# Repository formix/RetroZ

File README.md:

# RetroZ SBC S80
A minimalist single board Z80 retro computer based on the S80 design 
specifications.

This board is developped using the S80 physical specifications. The 
specifications are not currently available online but I plan to fix that in a 
future revision.

*Front of the board*

[Back of the board](https://raw.githubusercontent.com/formix/RetroZ/master/Documents/RetroZ-SBC-Back.png)

You can find the board schematic as a PDF [here](https://github.com/formix/RetroZ/blob/master/Documents/RetroZ-SBC.pdf).

## BOM

You can download the BOM [here](https://github.com/formix/RetroZ/blob/master/Projects/RetroZ-SBC/RetroZ-SBC-BOM.ods?raw=true). It is an Open Document Worksheet file and you should be able to open it with Open/Libre Office or MS Excel. If you have issue, contact me.

| Comp.                      | Mouser#  | Digikey#      | Mfr#               | Qty | Description                        | 
|----------------------------|----------|---------------|--------------------|-----|------------------------------------| 
| C1,C2                      |          |               | C317C200J5G5TA     | 2   | 20pf Capacitor                     | 
| C3,C4                      |          |               | FG28C0G1H470JNT06  | 2   | 47pF Capacitor                     | 
| C5,C6,C7,C8,C9,C10,C11,C12 |          |               | C322C104K5R5TA7301 | 8   | 0,1uF Capacitors                   | 
| D1                         |          |               | 151051VS04000      | 1   | Green Led 5mm                      | 
| D2,D3                      |          |               | 151031SS06000      | 2   | Red Led 3mm Round, FwdV 2.2        | 
| IC1                        |          |               | ADM803TAKSZ-REEL7  | 1   | Power-on Reset chip                | 
| IC2                        |          |               | AT28C256-15PU      | 1   | EEPROM 256kbit 28-Pin PDIP         | 
| IC2,IC3                    |          |               | 4828-6004-CP       | 2   | CONN IC DIP SOCKET 28POS TIN       | 
| IC3                        |          |               | AS6C62256-55PCN    | 1   | IC SRAM 256K PARALLEL 28DIP        | 
| J1                         | 485-2223 | 1528-1385-ND  | 2223               | 1   | Adafruit stacking header 2x20      | 
| J2,J3                      | 485-85   | 1528-1074-ND  | 85                 | 1   | STACKING HEADER ARDUINO SHIELD     | 
| J4                         |          |               | PRPC005DAAN-RC     | 1   | 5x2 Pin Connector                  | 
| J4,J6                      |          |               | QPC02SXGN-RC       | 2   | 1x2 Shunt connector                | 
| J5                         |          |               | 629105150521       | 1   | USB Microb B SMT Connector         | 
| J6                         |          |               | PRPC004DAAN-RC     | 1   | 4x2 Pin Connector                  | 
| R1                         |          |               | RNF14FTD1M00       | 1   | 1M Ohm Resistor                    | 
| R10,R11                    |          |               | RNF14FTD332R       | 2   | 332 Ohm resistor                   | 
| R2                         |          |               | RNF14FTD1K00       | 1   | 1k Ohm Resistor                    | 
| R3,R4,R5,R6,R12,R13,R14    |          |               | RNF14FTD10K0       | 7   | 10k Ohm Resistor                   | 
| R7                         |          |               | RNF14FTD221R       | 1   | 221 Ohm Resistor                   | 
| R8,R9                      |          |               | RNF14FTD27R4       | 2   | 27 Ohm Resistors                   | 
| SW2                        |          |               | BD01               | 1   | DIP Switch x1                      | 
| U1                         |          |               | 74LS32             | 1   | Quand OR                           | 
| U2                         |          |               | 74HCT04            | 1   | Hex Inverter Schmidt Trigger       | 
| U3                         |          |               | Z84C0008PEG        | 1   | Z80 CPU                            | 
| U3,U5                      |          |               | 4840-6004-CP       | 1   | 40 pin (2 x 20) DIP socket 15,24mm | 
| U4                         |          |               | SN74LS138N         | 1   | 3 to 8 Decoder/Demux               | 
| U5                         |          |               | Z84C4208PEG        | 1   | Z80 SIO/2                          | 
| U6                         |          |               | FT230XS-U          | 1   | UART to USB                        | 
| U7                         |          |               | 74LS92             | 1   | Dodecade counter (div. By 12)      | 
| Y1                         |          |               | ECS-73-20-5PX-TR   | 1   | 7,3728 MHz Crystal                 | 

## Development Note

### 2019-01-15
The review phase is done! I just sent the board to production. I should get the
finished board next week.

### 2019-01-26
I recieved my boards (10 boards!) yesterday. I just finished creating the BOM 
and sorted through my parts to order what is missing. I expect to recieve my 
order in the coming week. I'll work on the NASCOM Basic once I got the 
computer assembled. Stay tuned!

### 2019-08-03
It's been a while since I updated that README file but as you can see,
I'm committing regularily on the project. Simply put, I'm too busy playing 
with my working RetroZ SBC computer to update the front documentation. It is 
time to fix that, continue reading to get the full update.

## What's Inside?
The RetroZ-SBC computer is a 8MHz Z80 CPU clocked at 7.3728 MHz. It supports 
up to 32kB of ROM and 32kB of RAM. An SIO/2 chip is connected to the USB 
Micro B socket using an FTDI serial converter. Rx and Tx leds let you know 
when the computer communicates over USB. The whole computer is powered through
the same USB port and a power-on reset monitor resets the computer at startup.
A Reset button allows warm computer restart. An On/Off DIP switch controls the
power state of the computer and a power led indicator let you know that the 
beast is powered. All the Z80 processor pins are available through the 40 pins
stacking header plus some other on the User Port A. User Port B stacking
header is fully available (8 pins) for child boards future projects.

## The Connection
The USB to serial conversion is made possible thanks to an FTDI chip 
[behind the board](https://raw.githubusercontent.com/formix/RetroZ/master/Documents/RetroZ-SBC-Back.png) 
and is clocked at 115200 bauds by default. This speed can be changed 
programmatically through the Z84C40 (Zilog SIO/2) registers. On a Windows
machine the device can be accessed using **COM5**. For a 
Mac/Linux box it is **/dev/ttyUSB0**. Hardware flow control CTS/RTS is fully 
wired so feel free to flood the console with whatever you get, it should 
handle it.

## Technical Reference
### Power and commnunication over USB
Using a single USB Micro-B wire, it is possible to power-up and communicate 
with the computer. There is a DIP switch to set the computer on or off and a 
power indicator led indicates when the computer is powered on. There is also
a power line monitor chip (IC1) that pull the /RESET line LOW for 240 ms 
after power on.

### Serial Communication
Serial communication is achieved using a Z84C42 SIO/2 chip. The serial port A 
is connected to the USB jack through an FTDI UART to USB 2.0 converter. Rx 
and Tx leds indicate when communication occurs on that port. The serial port 
B is connected back into the User Port A (J2) PIN 2 (RxB) and Pin 3 (TxB) for 
slave cards serial communications.

**The serial port A clock** is directly tied to the clock and can be changed 
programmatically from the SIO/2 registers. In the NASCOM Basic provided, it is 
set to 115200 by default.

**The serial port B clock** The default speed is set to 115200 bauds as well. 
Again, that speed can be programmatically changed. The serial clock on port B 
goes through a dodecade counter and can be further adjusted using the 
`Clock div.` (J6) jumper that offers another set of 1,2,6 and 12 dividers. 
That gives a wide variety of standard baud rates down to 9600 bauds.

### Onboard memory control
The PIN 1 of the User Port A is pulled low with a 2k resistor. This is the 
on-board memory enable input pin (/ME). To disable onboard memory, an 
expansion card can set that pin HIGH. This would be the case with a memory 
expansion board. It can be hardwired to 5V to disable the onboard memory 
completely or it can be tied to some logic to leverage the on-board memory as 
needed.

### Interrupt Chaining
The RetroZ SBC design allows chaining interrupts of up to 4 slave boards. The
onboard SIO/2 IEO pin is hardwired to the User Port A INT0 (PIN 4). Its 
Interrupt Enable In pin can be tied to any of the other INT pins using the 
IEI Select jumper (J4). Selecting the first position of that jumper (INT0) 
sets the on-board SIO/2 as the Master. On slave boards, the Interrupt Enable 
In will have 6 positions. Also, a 4 positions IEO jumper header should be 
provided to select the right User Port A IEO position (pins 5-8). More on 
that on the slave board design document.

**WARNING** User Port A pins 4-8 (interrupts) are not protected. If you 
connect a daughter board without checking jumper settings first, you could 
short an IO pin on your stack and damage a chip! Looking into a solution to 
that in a future revision.

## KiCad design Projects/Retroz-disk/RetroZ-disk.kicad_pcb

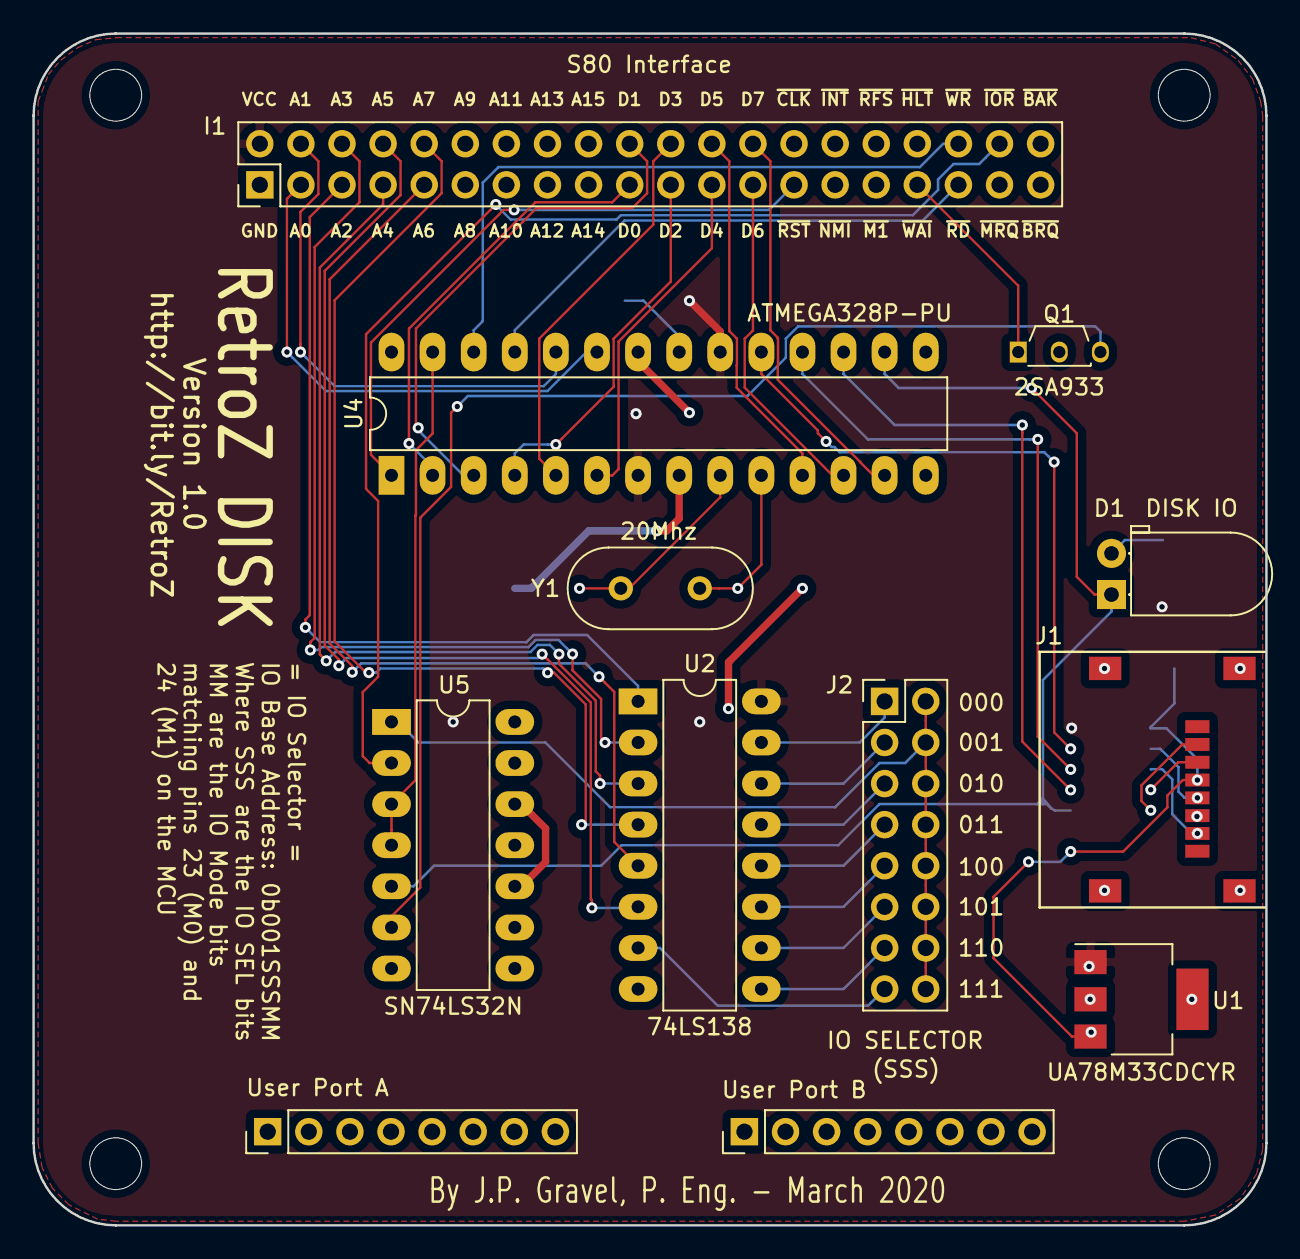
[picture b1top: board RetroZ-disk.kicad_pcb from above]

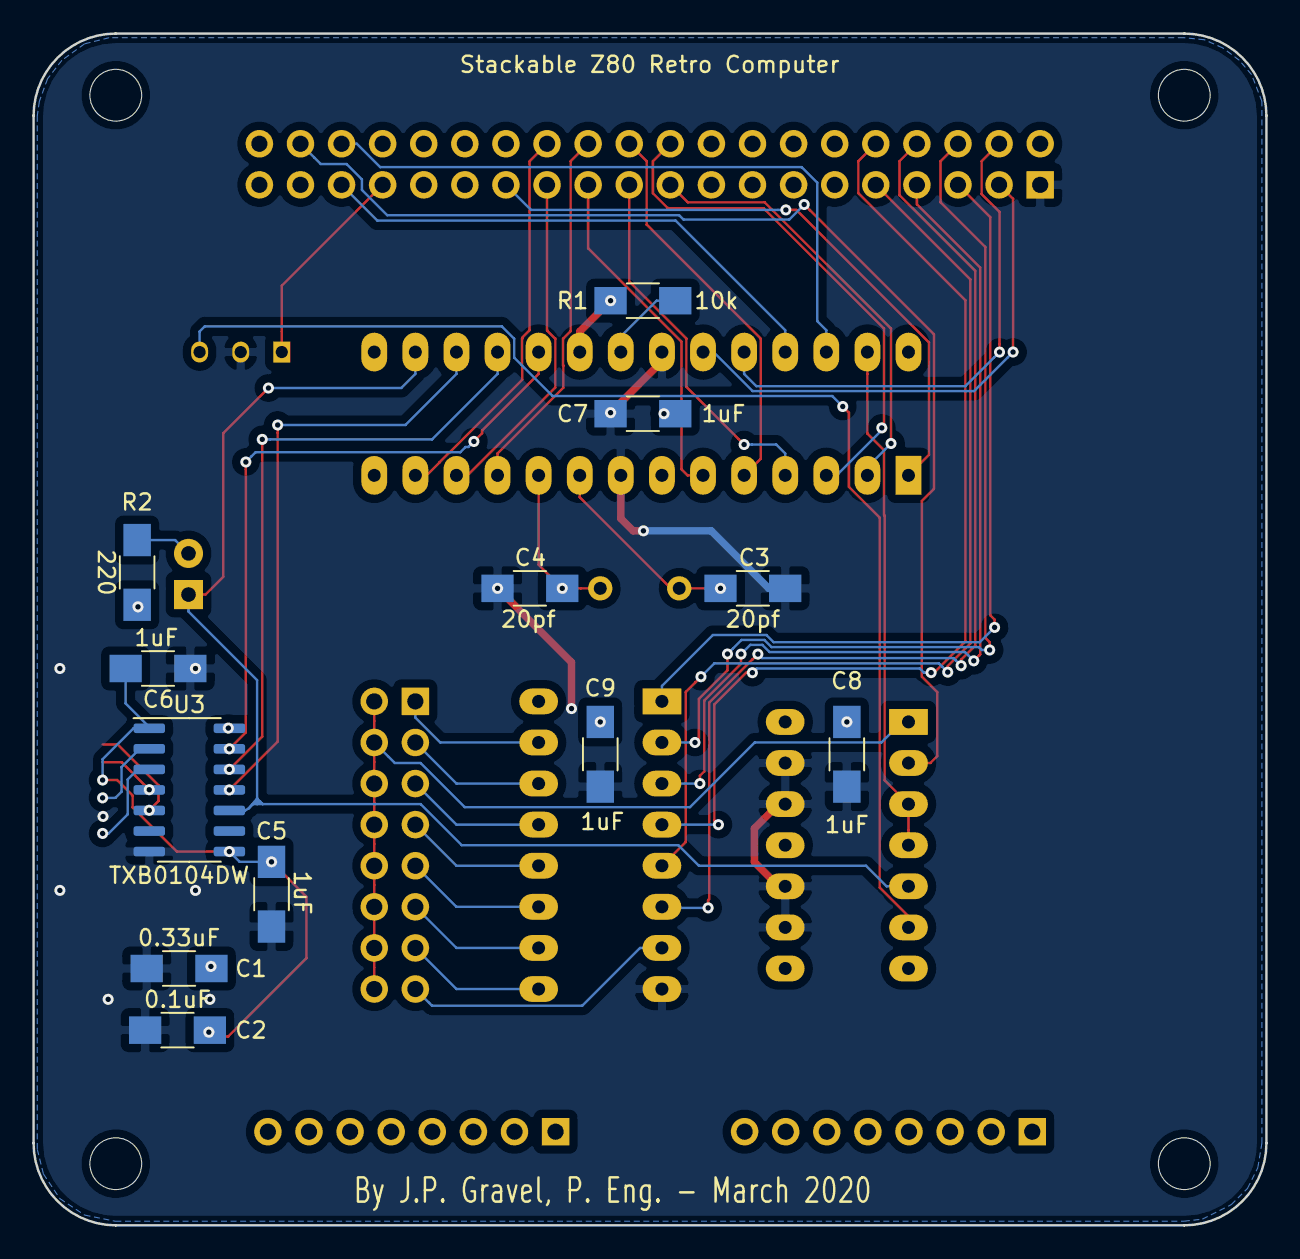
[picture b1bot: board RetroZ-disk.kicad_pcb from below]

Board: 2 copper layers, 76.2 x 73.7 mm, 22 parts (12 on the bottom side), 47 nets.

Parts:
C1: 0.33uF; R_1206_HandSoldering
C2: 0.1uF; R_1206_HandSoldering
C3, C4: 20pf; R_1206_HandSoldering
C5, C6, C7, C8, C9: 1uF; R_1206_HandSoldering
D1: DISK IO; LED_D5.0mm_Horizontal_O1.27mm_Z3.0mm
I1: S80 Interface; S80-1
J1: Micro_SD_Card; MicroSd_Wurth_693072010801
J2: IO SELECTOR; Pin_Header_Straight_2x08_Pitch2.54mm
Q1: 2SA933; TO-92S_Wide
R1: 10k; R_1206_HandSoldering
R2: 220; R_1206_HandSoldering
U1: UA78M33CDCYR; SOT-223-3_TabPin2
U2: 74LS138; DIP-16_W7.62mm_LongPads
U3: TXB0104DW; SOIC-14_3.9x8.7mm_P1.27mm
U4: ATMEGA328P-PU; DIP-28_W7.62mm_LongPads
U5: SN74LS32N; DIP-14_W7.62mm_LongPads
Y1: 20Mhz; Crystal_HC49-4H_Vertical

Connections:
/D0: I1.19, U4.2
/D1: I1.20, U4.3
/D2: I1.21, U4.4
/D3: I1.22, U4.5
/D4: I1.23, U4.6
/D5: I1.24, U4.11
/D6: I1.25, U4.12
/D7: I1.26, U4.13
/MISO: U3.12, U4.18
/MODE0: I1.3, U4.23
/MODE1: I1.4, U4.24
/MOSI: U3.11, U4.17
/SCK: U3.13, U4.19
/~CS: U4.27, U5.3, U5.4
/~IORQ: I1.38, U5.2
/~RD: I1.35, U4.25
/~RESET: I1.27, U4.1
/~SEL: J2.2, J2.4, J2.6, J2.8, J2.10, J2.12, J2.14, J2.16, U5.1
/~SS: D1.1, U3.10, U4.16, U5.5
/~WAIT: I1.33, Q1.1
/~WR: I1.36, U4.26
GND: C1.2, C2.2, C3.2, C4.2, C5.2, C6.2, C7.2, C8.2, C9.2, I1.1, J1.6, J1.9, Q1.2, U1.2, U2.8, U3.7, U4.8, U4.22, U5.9, U5.10, U5.12, U5.13
unnamed: C3.1, U4.9, Y1.2
unnamed: C4.1, U4.10, Y1.1
unnamed: D1.2, R2.2
unnamed: I1.5, U2.1
unnamed: I1.6, U2.2
unnamed: I1.7, U2.3
unnamed: I1.8, U2.6
unnamed: I1.9, U2.5
unnamed: I1.10, U2.4
unnamed: J1.2, U3.5
unnamed: J1.3, U3.4
unnamed: J1.5, U3.2
unnamed: J1.7, U3.3
unnamed: J2.1, U2.15
unnamed: J2.3, U2.14
unnamed: J2.5, U2.13
unnamed: J2.7, U2.12
unnamed: J2.9, U2.11
unnamed: J2.11, U2.10
unnamed: J2.13, U2.9
unnamed: J2.15, U2.7
unnamed: Q1.3, U5.6
unnamed: R1.1, U4.21
VCC: C1.1, C7.1, C8.1, C9.1, I1.2, R1.2, R2.1, U1.1, U2.16, U3.14, U4.7, U4.20
VDD: C2.1, C5.1, C6.1, J1.4, U1.3, U3.1, U3.8

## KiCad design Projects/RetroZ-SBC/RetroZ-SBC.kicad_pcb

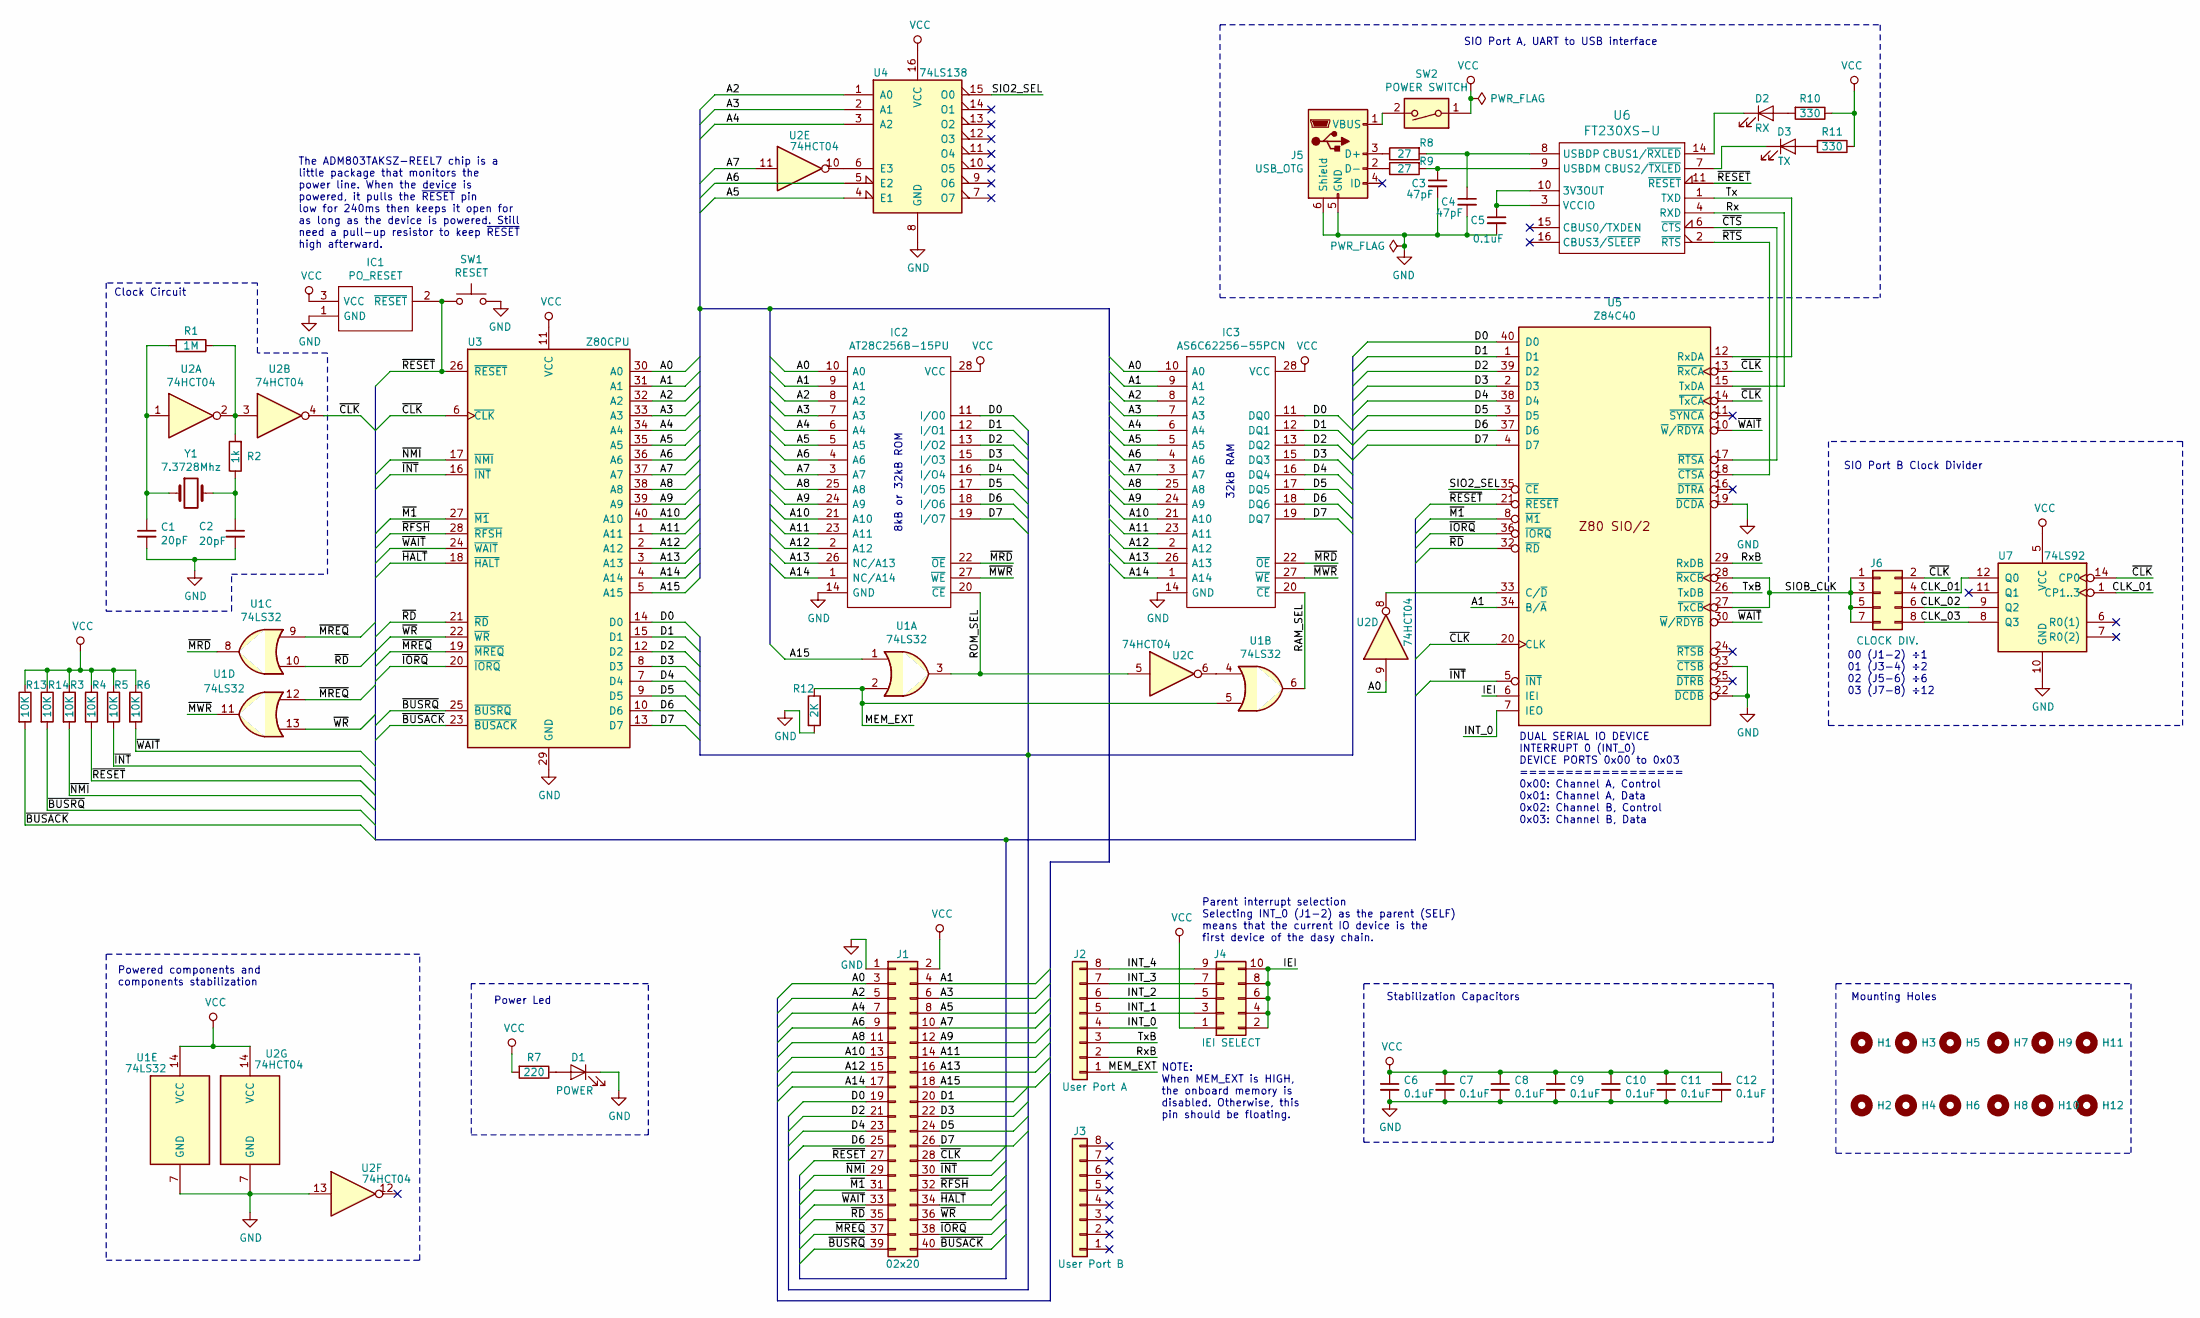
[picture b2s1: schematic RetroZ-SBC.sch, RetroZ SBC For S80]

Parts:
C1, C2: 20pF; C_Disc_D3.4mm_W2.1mm_P2.50mm; Mfr# C317C200J5G5TA
C3, C4: 47pF; C_Disc_D3.4mm_W2.1mm_P2.50mm; Mfr# FG28C0G1H470JNT06
C5, C6, C7, C8, C9, C10, C11, C12: 0.1uF; C_Disc_D3.4mm_W2.1mm_P2.50mm; Mfr# C322C104K5R5TA7301
D1: POWER; LED_D5.0mm_Horizontal_O1.27mm_Z3.0mm; Mfr# 151051VS04000
D2: RX; LED_D3.0mm_Horizontal_O1.27mm_Z2.0mm; Mfr# 151031SS06000
D3: TX; LED_D3.0mm_Horizontal_O1.27mm_Z2.0mm; Mfr# 151031SS06000
H1, H2, H3, H4, H5, H6, H7, H8, H9, H10, H11, H12: MountingHole; MountingHole_3.2mm_M3
IC1: PO_RESET; SOT-23; Mfr# ADM803TAKSZ-REEL7
IC2: AT28C256B-15PU; DIP-28_W15.24mm; Mouser Part Number 556-AT28C25615PU
IC3: AS6C62256-55PCN; DIP-28_W15.24mm; Mouser Part Number 913-AS6C62256-55PCN
J1: 02x20; Pin_Header_Straight_2x20_Pitch2.54mm; Mfr# 2223
J2: User Port A; Pin_Header_Straight_1x08_Pitch2.54mm
J3: User Port B; Pin_Header_Straight_1x08_Pitch2.54mm
J4: IEI SELECT; Pin_Header_Straight_2x05_Pitch2.54mm; Mfr# PRPC005DAAN-RC
J5: USB_OTG; USB_Micro-B_Wuerth-629105150521_CircularHoles; Mfr# 629105150521
J6: CLOCK DIV.; Pin_Header_Straight_2x04_Pitch2.54mm; Mfr# PRPC004DAAN-RC
R1: 1M; R_Axial_DIN0207_L6.3mm_D2.5mm_P10.16mm_Horizontal; Mfr# RNF14FTD1M00
R2: 1k; R_Axial_DIN0207_L6.3mm_D2.5mm_P10.16mm_Horizontal; Mfr# RNF14FTD1K00
R3, R4, R5, R6, R13, R14: 10K; R_Axial_DIN0207_L6.3mm_D2.5mm_P10.16mm_Horizontal; Mfr# RNF14FTD10K0
R7: 220; R_Axial_DIN0204_L3.6mm_D1.6mm_P2.54mm_Vertical; Mfr# RNF14FTD221R
R8, R9: 27; R_Axial_DIN0204_L3.6mm_D1.6mm_P2.54mm_Vertical; Mfr# RNF14FTD27R4
R10, R11: 330; R_Axial_DIN0204_L3.6mm_D1.6mm_P2.54mm_Vertical; Mfr# RNF14FTD330R
R12: 2K; R_Axial_DIN0207_L6.3mm_D2.5mm_P10.16mm_Horizontal; Mfr# RNF14FTD10K0
SW1: RESET; SW_PUSH_6mm_h5mm; Mfr# MJTP1230
SW2: POWER SWITCH; SW_DIP_x1_W7.62mm_Slide; Mfr# BD01
U1: 74LS32; DIP-14_W7.62mm
U2: 74HCT04; DIP-14_W7.62mm; Mfr# 74HCT04
U3: Z80CPU; DIP-40_W15.24mm; Mfr# Z84C0008PEG
U4: 74LS138; DIP-16_W7.62mm; Mfr# SN74LS138N
U5: Z84C40; DIP-40_W15.24mm; Mfr# Z84C4208PEG
U6: FT230XS-U; TSSOP-16_4.4x5mm_Pitch0.65mm; Mfr# FT230XS-U
U7: 74LS92; DIP-14_W7.62mm; Mfr# 74LS92
Y1: 7.3728Mhz; Crystal_SMD_SeikoEpson_MC405-2pin_9.6x4.1mm_HandSoldering; Mfr# ECS-73-20-5PX-TR

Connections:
/A0: IC2.10 (A0), IC3.10 (A0), J1.3, U2.9, U3.30 (A0)
/A1: IC2.9 (A1), IC3.9 (A1), J1.4, U3.31 (A1), U5.34 (B/~A)
/A2: IC2.8 (A2), IC3.8 (A2), J1.5, U3.32 (A2), U4.1 (A0)
/A3: IC2.7 (A3), IC3.7 (A3), J1.6, U3.33 (A3), U4.2 (A1)
/A4: IC2.6 (A4), IC3.6 (A4), J1.7, U3.34 (A4), U4.3 (A2)
/A5: IC2.5 (A5), IC3.5 (A5), J1.8, U3.35 (A5), U4.4 (E1)
/A6: IC2.4 (A6), IC3.4 (A6), J1.9, U3.36 (A6), U4.5 (E2)
/A7: IC2.3 (A7), IC3.3 (A7), J1.10, U2.11, U3.37 (A7)
/A8: IC2.25 (A8), IC3.25 (A8), J1.11, U3.38 (A8)
/A9: IC2.24 (A9), IC3.24 (A9), J1.12, U3.39 (A9)
/A10: IC2.21 (A10), IC3.21 (A10), J1.13, U3.40 (A10)
/A11: IC2.23 (A11), IC3.23 (A11), J1.14, U3.1 (A11)
/A12: IC2.2 (A12), IC3.2 (A12), J1.15, U3.2 (A12)
/A13: IC2.26 (NC/A13), IC3.26 (A13), J1.16, U3.3 (A13)
/A14: IC2.1 (NC/A14), IC3.1 (A14), J1.17, U3.4 (A14)
/A15: J1.18, U1.1, U3.5 (A15)
/CLK_01: J6.4, U7.1 (CP1..3), U7.12 (Q0)
/CLK_02: J6.6, U7.9 (Q2)
/CLK_03: J6.8, U7.8 (Q3)
/D0: IC2.11 (I/O0), IC3.11 (DQ0), J1.19, U3.14 (D0), U5.40 (D0)
/D1: IC2.12 (I/O1), IC3.12 (DQ1), J1.20, U3.15 (D1), U5.1 (D1)
/D2: IC2.13 (I/O2), IC3.13 (DQ2), J1.21, U3.12 (D2), U5.39 (D2)
/D3: IC2.15 (I/O3), IC3.15 (DQ3), J1.22, U3.8 (D3), U5.2 (D3)
/D4: IC2.16 (I/O4), IC3.16 (DQ4), J1.23, U3.7 (D4), U5.38 (D4)
/D5: IC2.17 (I/O5), IC3.17 (DQ5), J1.24, U3.9 (D5), U5.3 (D5)
/D6: IC2.18 (I/O6), IC3.18 (DQ6), J1.25, U3.10 (D6), U5.37 (D6)
/D7: IC2.19 (I/O7), IC3.19 (DQ7), J1.26, U3.13 (D7), U5.4 (D7)
/IEI: J4.2, J4.4, J4.6, J4.8, J4.10, U5.6 (IEI)
/INT_0: J2.4, U5.7 (IEO)
/INT_1: J2.5, J4.3
/INT_2: J2.6, J4.5
/INT_3: J2.7, J4.7
/INT_4: J2.8, J4.9
/MEM_EXT: J2.1, R12.1, U1.2, U1.5
/RAM_SEL: IC3.20 (~CE), U1.6
/ROM_SEL: IC2.20 (~CE), U1.3, U2.5
/Rx: U5.15 (TxDA), U6.4 (RXD)
/RxB: J2.2, U5.29 (RxDB)
/SIO2_SEL: U4.15 (O0), U5.35 (~CE)
/SIOB_CLK: J6.1, J6.3, J6.5, J6.7, U5.27 (~TxCB), U5.28 (~RxCB)
/Tx: U5.12 (RxDA), U6.1 (TXD)
/TxB: J2.3, U5.26 (TxDB)
/~BUSACK: J1.40, R13.2, U3.23 (~BUSACK~)
/~BUSRQ: J1.39, R14.2, U3.25 (~BUSRQ~)
/~CLK: J1.28, J6.2, U2.4, U3.6 (~CLK~), U5.13 (~RxCA), U5.14 (~TxCA), U5.20 (CLK), U7.14 (CP0)
/~CTS: U5.17 (~RTSA), U6.6 (~CTS)
/~HALT: J1.34, U3.18 (~HALT~)
/~INT: J1.30, R5.2, U3.16 (~INT~), U5.5 (~INT)
/~IORQ: J1.38, U3.20 (~IORQ~), U5.36 (~IORQ)
/~M1: J1.31, U3.27 (~M1~), U5.8 (~M1)
/~MRD: IC2.22 (~OE), IC3.22 (~OE), U1.8
/~MREQ: J1.37, U1.9, U1.12, U3.19 (~MREQ~)
/~MWR: IC2.27 (~WE), IC3.27 (~WE), U1.11
/~NMI: J1.29, R3.2, U3.17 (~NMI~)
/~RD: J1.35, U1.10, U3.21 (~RD~), U5.32 (~RD)
/~RESET: IC1.2 (~RESET), J1.27, R4.2, SW1.2, U3.26 (~RESET~), U5.21 (~RESET), U6.11 (~RESET)
/~RFSH: J1.32, U3.28 (~RFSH~)
/~RTS: U5.18 (~CTSA), U6.2 (~RTS)
/~WAIT: J1.33, R6.2, U3.24 (~WAIT~), U5.10 (~W~/~RDYA~), U5.30 (~W~/~RDYB)
/~WR: J1.36, U1.13, U3.22 (~WR~)
GND: C1.2, C2.2, C3.2, C4.2, C5.2, C6.2, C7.2, C8.2, C9.2, C10.2, C11.2, C12.2, D1.1 (K), IC1.1 (GND), IC2.14 (GND), IC3.14 (GND), J1.1, J5.5 (GND), J5.6 (Shield), R12.2, SW1.1, U1.7 (GND), U2.7 (GND), U2.13, U3.29 (GND), U4.8 (GND), U5.19 (~DCDA), U5.22 (~DCDB), U5.23 (~CTSB), U5.31 (GND), U6.5 (GND), U6.13 (GND), U7.10 (GND)
unnamed: C1.1, R1.2, U2.1, Y1.1
unnamed: C2.1, R2.1, Y1.2
unnamed: C3.1, R9.2, U6.9 (USBDM)
unnamed: C4.1, R8.2, U6.8 (USBDP)
unnamed: C5.1, U6.3 (VCCIO), U6.10 (3V3OUT)
unnamed: D1.2 (A), R7.1
unnamed: D2.1 (K), U6.14 (CBUS1/~RXLED)
unnamed: D2.2 (A), R10.2
unnamed: D3.1 (K), U6.7 (CBUS2/~TXLED)
unnamed: D3.2 (A), R11.2
unnamed: J5.1 (VBUS), SW2.2
unnamed: J5.2 (D-), R9.1
unnamed: J5.3 (D+), R8.1
unnamed: R1.1, R2.2, U2.2, U2.3
unnamed: U1.4, U2.6
unnamed: U2.8, U5.33 (C/~D)
unnamed: U2.10, U4.6 (E3)
VCC: C6.1, C7.1, C8.1, C9.1, C10.1, C11.1, C12.1, IC1.3 (VCC), IC2.28 (VCC), IC3.28 (VCC), J1.2, J4.1, R3.1, R4.1, R5.1, R6.1, R7.2, R10.1, R11.1, R13.1, R14.1, SW2.1, U1.14 (VCC), U2.14 (VCC), U3.11 (VCC), U4.16 (VCC), U5.9 (VCC), U6.12 (VCC), U7.5 (VCC)

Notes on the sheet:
8kB or 32kB ROM
32kB RAM
00 (J1-2) ÷1 01 (J3-4) ÷2 02 (J5-6) ÷6 03 (J7-8) ÷12
DUAL SERIAL IO DEVICE INTERRUPT 0 (INT_0) DEVICE PORTS 0x00 to 0x03 ================== 0x00: Channel A, Control 0x01: Channel A, Data 0x02: Channel B, Control 0x03: Channel B, Data
Parent interrupt selection Selecting INT_0 (J1-2) as the parent (SELF) means that the current IO device is the first device of the dasy chain.
Stabilization Capacitors
Mounting Holes
Power Led
Powered components and components stabilization
SIO Port A, UART to USB interface
SIO Port B Clock Divider
NOTE: When MEM_EXT is HIGH, the onboard memory is disabled. Otherwise, this pin should be floating.
The ADM803TAKSZ-REEL7 chip is a little package that monitors the power line. When the device is powered, it pulls the ~RESET~ pin low for 240ms then keeps it open for as long as the device is powered. Still need a pull-up resistor to keep ~RESET~ high afterward.
Clock Circuit

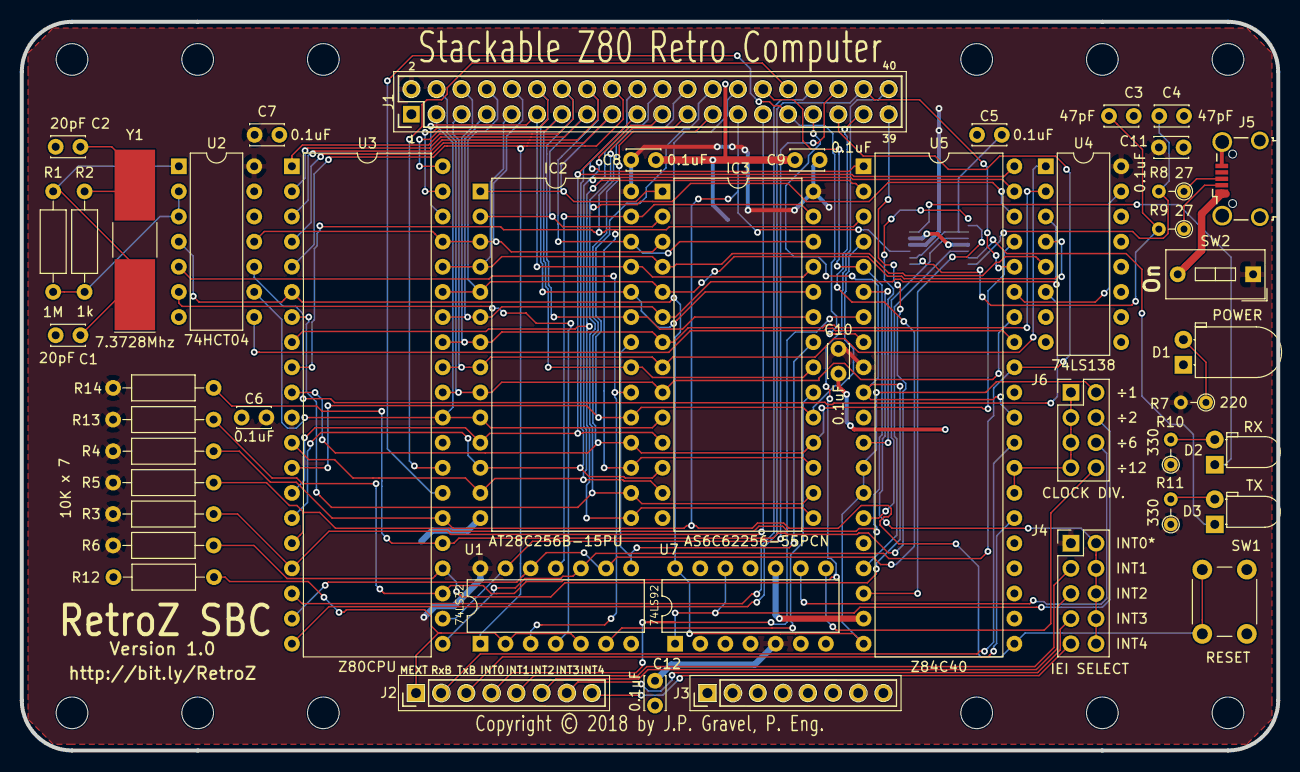
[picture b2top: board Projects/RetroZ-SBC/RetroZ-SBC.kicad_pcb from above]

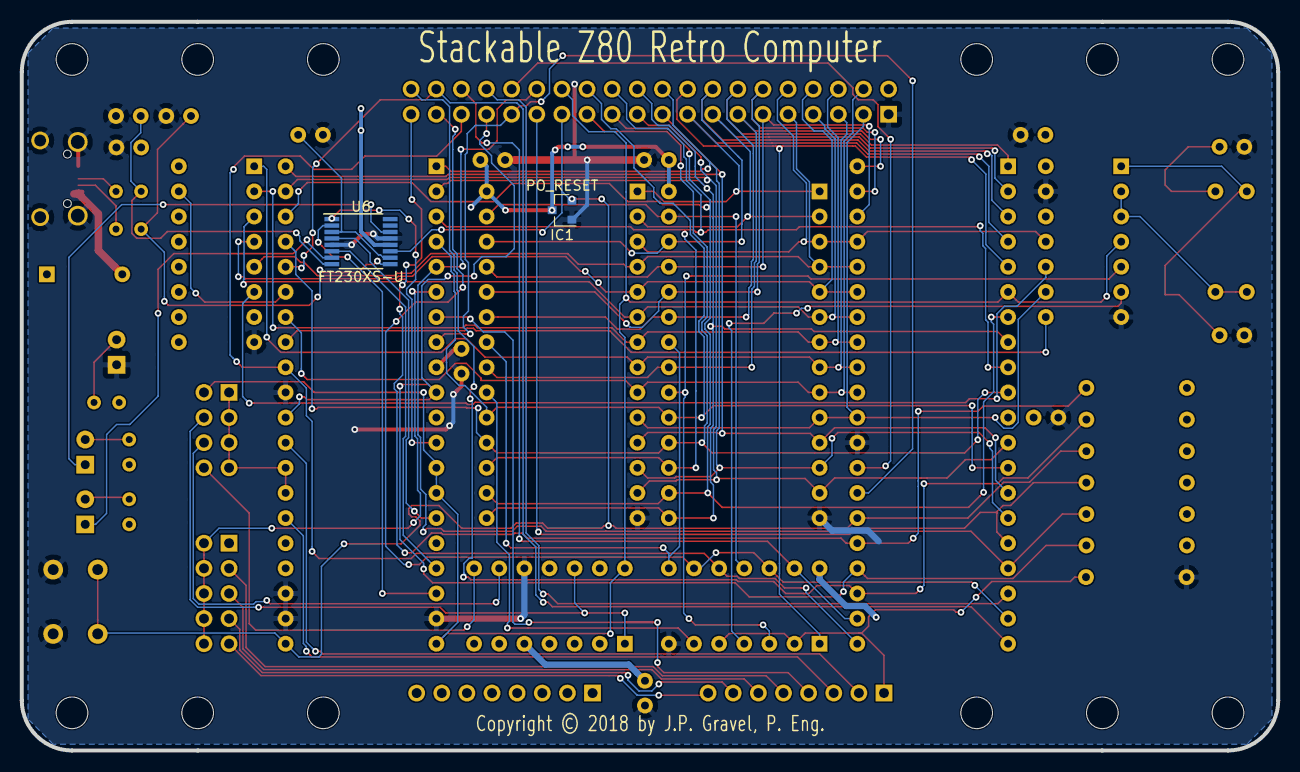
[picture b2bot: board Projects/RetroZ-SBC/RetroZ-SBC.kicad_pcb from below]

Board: 2 copper layers, 127.0 x 73.7 mm, 60 parts (2 on the bottom side), 79 nets.

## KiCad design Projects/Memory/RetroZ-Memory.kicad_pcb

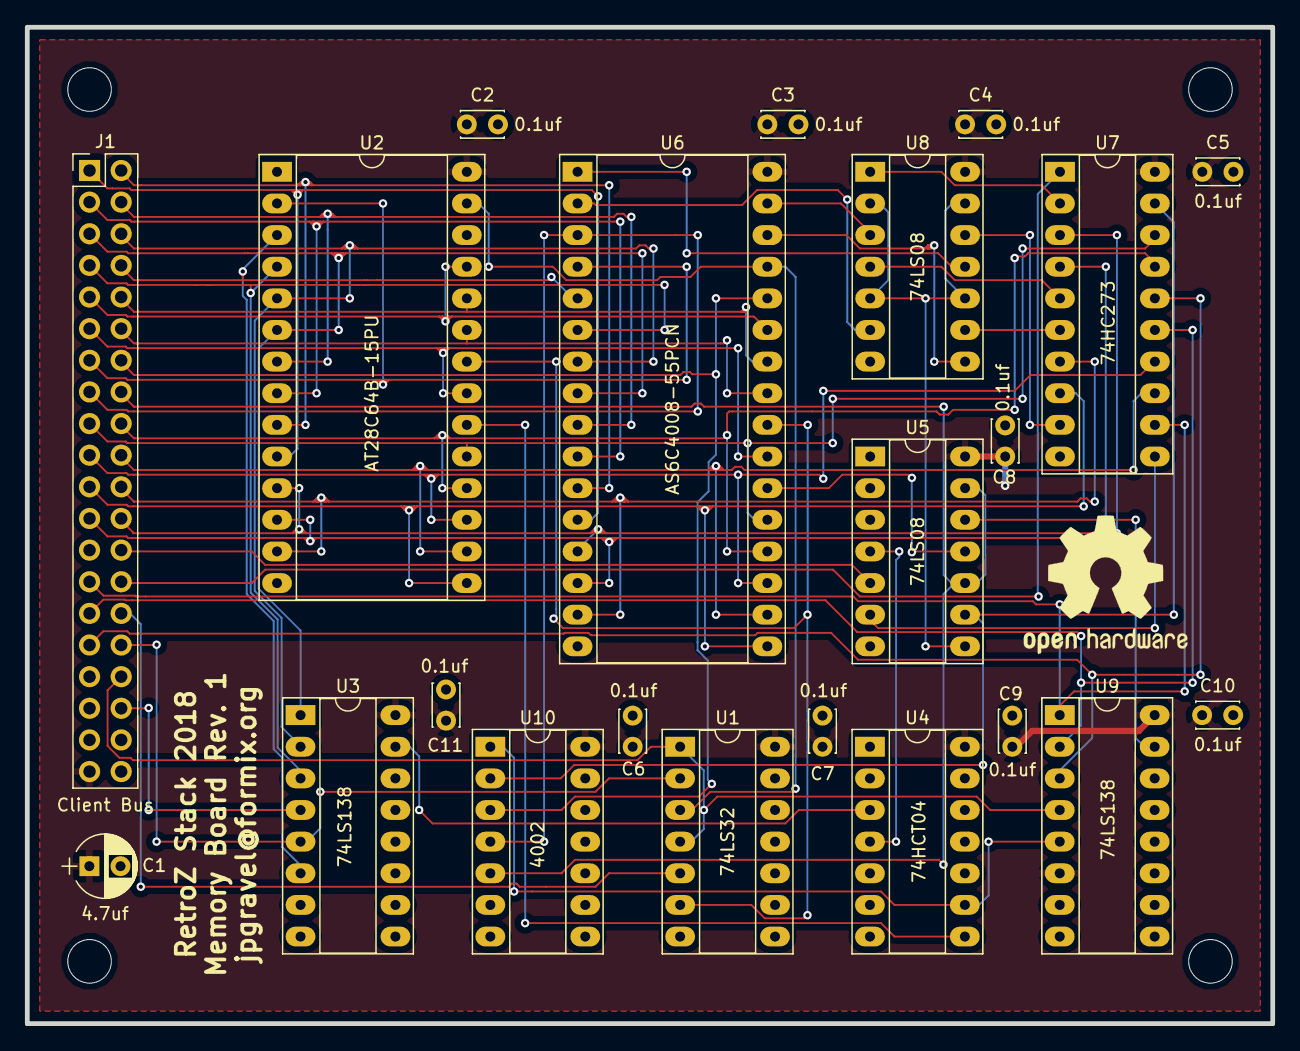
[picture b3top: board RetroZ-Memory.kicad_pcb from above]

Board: 2 copper layers, 100.0 x 80.0 mm, 22 parts (0 on the bottom side), 54 nets.

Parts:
C1: 4.7uf; CP_Radial_D5.0mm_P2.50mm
C2, C3, C4, C5, C6, C7, C8, C9, C10, C11: 0.1uf; C_Disc_D3.4mm_W2.1mm_P2.50mm
J1: Client Bus; Pin_Header_Straight_2x20_Pitch2.54mm
U1: 74LS32; DIP-14_W7.62mm_Socket_LongPads
U2: AT28C64B-15PU; DIP-28_W15.24mm_Socket_LongPads
U3, U9: 74LS138; DIP-16_W7.62mm_Socket_LongPads
U4: 74HCT04; DIP-14_W7.62mm_Socket_LongPads
U5, U8: 74LS08; DIP-14_W7.62mm_Socket_LongPads
U6: AS6C4008-55PCN; DIP-32_W15.24mm_Socket_LongPads
U7: 74HC273; DIP-20_W7.62mm_Socket_LongPads
U10: 4002; DIP-14_W7.62mm_Socket_LongPads

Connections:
/A0: J1.1, U2.10, U6.12
/A1: J1.2, U2.9, U6.11
/A2: J1.3, U2.8, U6.10
/A3: J1.4, U2.7, U6.9
/A4: J1.5, U2.6, U3.1, U6.8
/A5: J1.6, U2.5, U3.2, U6.7
/A6: J1.7, U2.4, U3.3, U6.6
/A7: J1.8, U2.3, U3.6, U6.5
/A8: J1.9, U2.25, U6.27
/A9: J1.10, U2.24, U6.26
/A10: J1.11, U2.21, U6.23
/A11: J1.12, U2.23, U6.25
/A12: J1.13, U2.2, U6.4
/A13: J1.14, U6.28, U10.3
/A14: J1.15, U6.3, U10.4
/D0: J1.24, U2.11, U6.13, U7.3
/D1: J1.23, U2.12, U6.14, U7.4
/D2: J1.22, U2.13, U6.15, U7.7
/D3: J1.21, U2.15, U6.17, U7.8
/D4: J1.20, U2.16, U6.18, U7.13
/D5: J1.19, U2.17, U6.19, U7.14
/D6: J1.18, U2.18, U6.20, U7.17
/D7: J1.17, U2.19, U6.21, U7.18
/~RAMS: U4.9, U9.5, U10.1
A15: J1.16, U5.10, U5.13, U10.5
CLK: J1.26, U5.5
DMA0: J1.27, U7.12, U9.1
DMA1: J1.29, U7.15, U9.2
DMA2: J1.31, U7.16, U9.3
GND: C1.2, C2.2, C3.2, C4.2, C5.2, C6.2, C7.2, C8.2, C9.2, C10.2, C11.2, J1.40, U1.7, U2.14, U3.8, U4.7, U5.7, U6.16, U7.10, U8.7, U9.8, U10.7
unnamed: J1.30, U1.5
unnamed: U3.15, U4.3
unnamed: U4.4, U5.4
unnamed: U5.6, U7.11
unnamed: U5.8, U8.2, U8.5, U8.10, U8.13
unnamed: U5.12, U9.15
unnamed: U7.2, U8.1
unnamed: U7.5, U8.4
unnamed: U7.6, U8.9
unnamed: U7.9, U8.12
RAMONLY: U5.9, U7.19, U10.2
RAM_A15: U6.31, U8.3
RAM_A16: U6.2, U8.6
RAM_A17: U6.30, U8.8
RAM_A18: U6.1, U8.11
VCC: C1.1, C2.1, C3.1, C4.1, C5.1, C6.1, C7.1, C8.1, C9.1, C10.1, C11.1, J1.39, U1.14, U2.28, U3.16, U4.14, U5.14, U6.32, U7.20, U8.14, U9.6, U9.16, U10.14
~IORQ: J1.36, U3.4
~MRD: U1.6, U2.22, U6.24
~MREQ: J1.34, U1.1, U1.4, U9.4
~MWR: U1.3, U2.27, U6.29
~RAM_SEL: U5.11, U6.22
~RESET: J1.28, U7.1
~ROM_SEL: U2.20, U4.8
~WR: J1.32, U1.2, U3.5

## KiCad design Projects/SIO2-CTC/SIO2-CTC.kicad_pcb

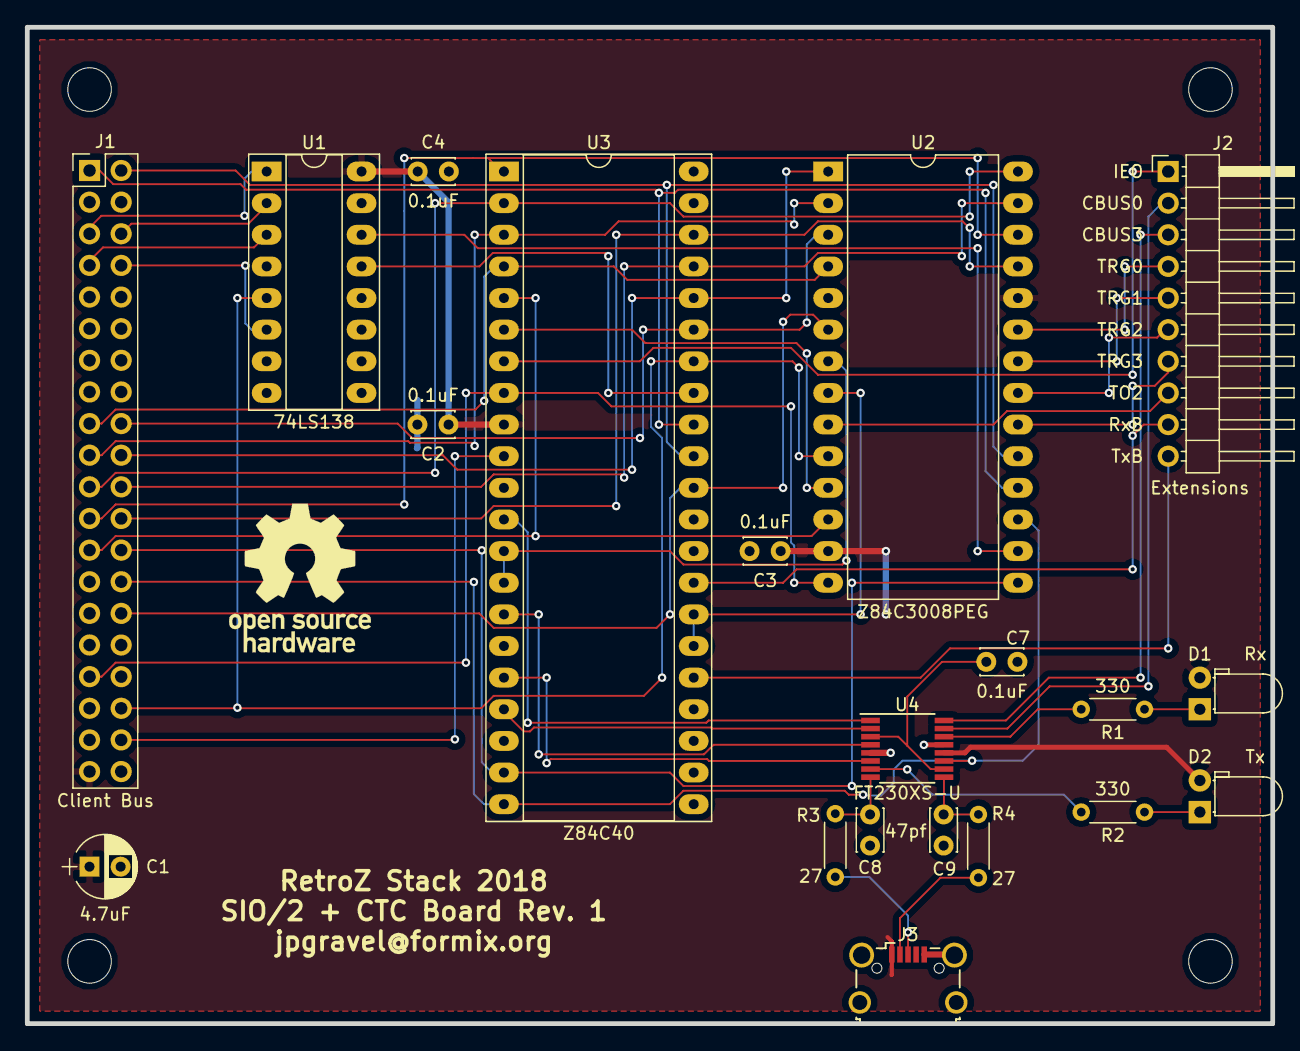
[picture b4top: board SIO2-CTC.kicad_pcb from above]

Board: 2 copper layers, 100.0 x 80.0 mm, 20 parts (0 on the bottom side), 51 nets.

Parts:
C1: 4.7uF; CP_Radial_D5.0mm_P2.50mm
C2, C3, C4, C7: 0.1uF; C_Disc_D3.4mm_W2.1mm_P2.50mm
C8, C9: 47pf; C_Disc_D3.4mm_W2.1mm_P2.50mm
D1: Rx; LED_D3.0mm_Horizontal_O1.27mm_Z2.0mm
D2: Tx; LED_D3.0mm_Horizontal_O1.27mm_Z2.0mm
J1: Client Bus; Pin_Header_Straight_2x20_Pitch2.54mm
J2: Extensions; Pin_Header_Angled_1x10_Pitch2.54mm
J3: USB_OTG; USB_Micro-B_Wuerth-629105150521_CircularHoles
R1, R2: 330; R_Axial_DIN0204_L3.6mm_D1.6mm_P5.08mm_Horizontal
R3, R4: 27; R_Axial_DIN0204_L3.6mm_D1.6mm_P5.08mm_Horizontal
U1: 74LS138; DIP-16_W7.62mm_Socket_LongPads
U2: Z84C3008PEG; DIP-28_W15.24mm_LongPads
U3: Z84C40; DIP-42_W15.24mm_Socket_LongPads
U4: FT230XS-U; TSSOP-16_4.4x5mm_Pitch0.65mm

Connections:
/A4: J1.5, U1.1
/A5: J1.6, U1.2
/A6: J1.7, U1.3
/A7: J1.8, U1.6
/CBUS0: J2.2, U4.15
/CBUS3: J2.3, U4.16
/CLK/TRG0: J2.4, U2.23
/CLK/TRG1: J2.5, U2.22
/CLK/TRG2: J2.6, U2.21
/CLK/TRG3: J2.7, U2.20
/D0: J1.24, U2.25, U3.40
/D1: J1.23, U2.26, U3.1
/D2: J1.22, U2.27, U3.39
/D3: J1.21, U2.28, U3.2
/D4: J1.20, U2.1, U3.38
/D5: J1.19, U2.2, U3.3
/D6: J1.18, U2.3, U3.37
/D7: J1.17, U2.4, U3.4
/D+: J3.3, R3.1
/D-: J3.2, R4.1
/RxA: U3.12, U4.1
/RxLED: R1.2, U4.14
/TxA: U3.15, U4.4
/TxLED: R2.2, U4.7
/USBDM: C9.1, R4.2, U4.9
/USBDP: C8.1, R3.2, U4.8
/ZC/TO2: J2.8, U2.9
/~CTSA: U3.18, U4.2
/~RTSA: U3.17, U4.6
/~SEL_SIO2: U1.13, U3.35
A0: J1.1, U2.18, U3.34
A1: J1.2, U2.19, U3.33
CLK: J1.26, U2.15, U3.20
GND: C1.2, C2.2, C3.2, C4.2, C7.2, C8.2, C9.2, J1.40, J3.5, J3.6, U1.4, U1.8, U2.5, U3.31, U4.5, U4.13
IEO: J2.1, U3.7
INT_EN: U2.11, U3.6
unnamed: C7.1, U4.3, U4.10
unnamed: D1.1, R1.1
unnamed: D2.1, R2.1
unnamed: U2.7, U3.13, U3.14
unnamed: U2.8, U3.27, U3.28
RxB: J2.9, U3.29
TxB: J2.10, U3.26
VCC: C1.1, C2.1, C3.1, C4.1, D1.2, D2.2, J1.39, J3.1, U1.16, U2.13, U2.24, U3.9, U4.12
~INT: J1.25, U2.12, U3.5
~IORQ: J1.36, U1.5, U2.10, U3.36
~M1: J1.33, U2.14, U3.8
~RD: J1.30, U2.6, U3.32
~RESET: J1.28, U2.17, U3.21, U4.11
~SEL_CTC: U1.14, U2.16
~WAIT: J1.38, U3.10

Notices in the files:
Projects/RetroZ-SBC/RetroZ-SBC.kicad_pcb:
Copyright (c) 2018 by J.P. Gravel, P. eng.
Copyright © 2018 by J.P. Gravel, P. Eng.
